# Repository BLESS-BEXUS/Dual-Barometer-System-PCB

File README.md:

<p align="center">
    <br>
    
</p>
<h1 align="center">Dual-Barometer System</h1>
<p align="center">
A compact PCB designed to provide wide-range pressure measurement, redundant sensing and onboard calibration for embedded systems where reliability, accuracy and easy integration are key.
</p>

<p align="center">

    <br>
    
</p>

---

### Overview

The main goal of this PCB is to improve the reliability and accuracy of pressure measurement in embedded sensing systems.

It is especially useful in applications where pressure conditions may vary significantly during operation and where a single commercial sensor may not provide enough range, resolution or calibration stability.

The board is designed to support:

- Wide-range pressure measurement.
- Redundant pressure sensing.
- Altitude estimation.
- Sensor cross-validation.
- Onboard calibration storage.
- Easy integration with a main controller.

### Main Features

- Dual-barometer architecture.
- TE MS5803-01BA high-resolution pressure sensor.
- Amphenol NPA-730B low-pressure backup sensor.
- Shared I2C communication bus.
- Onboard Microchip 24LC02B EEPROM.
- Storage of board-specific calibration coefficients.
- Plug-and-play calibration approach.
- Compact PCB for embedded sensing applications.
- Custom KiCad symbols, footprints and 3D models.

---

<h3 align="center">Contributing</h3>

<p align="center">
·
    <a href="./CODE_OF_CONDUCT.md">Code of Conduct</a>
    ·
    <a href="./CONTRIBUTING.md">Contributing Guide</a>
    ·
</p>

<p align="center">We welcome collaboration from the aerospace and software community. For major changes or data inquiries, please open an issue first.</p>

<h3 align="center">License</h3>

<pre align="center">Copyright © 2025-2026 The BLESS Project Team<br><br>This Source Code Form is subject to the terms of the Mozilla Public<br>License, v. 2.0. If a copy of the MPL was not distributed with this<br>file, You can obtain one at http://mozilla.org/MPL/2.0/.</pre>

<h3 align="center">Credits & Team</h3>

<p align="center">Supported by the REXUS/BEXUS Program and our generous sponsors.</p>
<p align="center">
    
</p>

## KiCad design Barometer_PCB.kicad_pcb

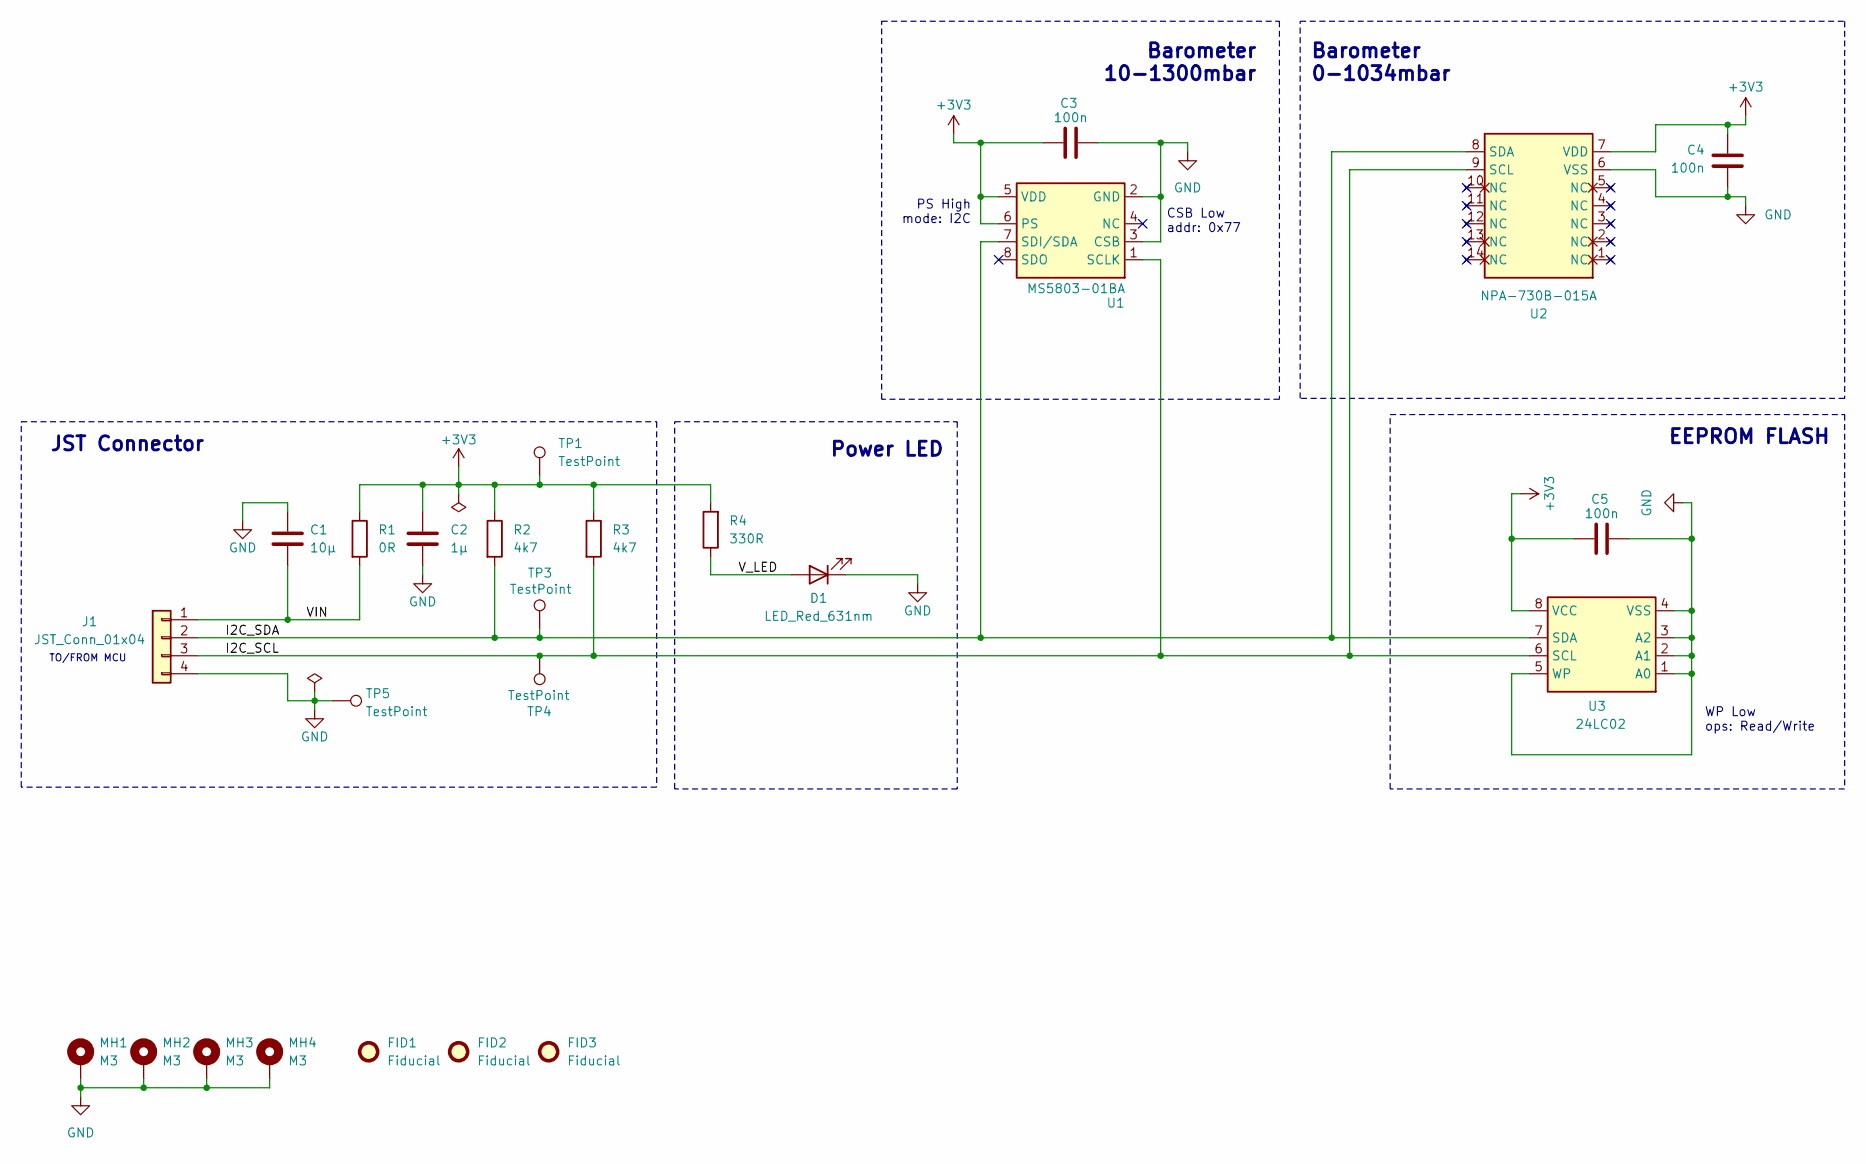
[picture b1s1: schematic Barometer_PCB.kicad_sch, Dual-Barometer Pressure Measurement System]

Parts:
C1: 10µ; C_1206_3216Metric; Manufacturer Part Number CGA5L1X7R1C106K160AC; LCSC C2168241
C2: 1µ; C_0805_2012Metric; Manufacturer Part Number KGM21AR71C105JU; LCSC C20219896
C3, C4, C5: 100n; C_0805_2012Metric; Manufacturer Part Number GCD21BR71H104KA01K; LCSC C21025875
D1: LED_Red_631nm; LED_0603_1608Metric; Manufacturer Part Number LTST-C190KRKT; LCSC C94869
FID1, FID2, FID3: Fiducial; Fiducial_1mm_Mask2mm
J1: JST_Conn_01x04; JST_SH_BM04B-SRSS-TB_1x04-1MP_P1.00mm_Vertical; Manufacturer Part Number BM04B-SRSS-TB(LF)(SN); LCSC C160390
MH1, MH2, MH3, MH4: M3; MountingHole_3.2mm_M3_Pad_Via
R1: 0R; R_0603_1608Metric; Manufacturer Part Number RC0603JR-070RL; LCSC C95177
R2, R3: 4k7; R_0805_2012Metric; Manufacturer Part Number AC0805JR-134K7L; LCSC C6457914
R4: 330R; R_0603_1608Metric; Manufacturer Part Number CR0603-FX-3300ELF; LCSC C2077087
TP1, TP3, TP4, TP5: TestPoint; TestPoint_Pad_D1.0mm
U1: MS5803-01BA; Manufacturer Part Number MS580301BA01-00; LCSC C5166409
U2: NPA-730B-015A; SOIC-14W_7.5x9mm_P1.27mm; Manufacturer Part Number NPA-730B-015A; LCSC C3253841
U3: 24LC02; SOIC-8_3.9x4.9mm_P1.27mm; Manufacturer Part Number 24LC02B-I/SN; LCSC C1348870

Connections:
+3V3: C2.1, C3.1, C4.1, C5.1, R1.1, R2.1, R3.1, R4.2, TP1.1, U1.5 (VDD), U1.6 (PS), U2.7 (VDD), U3.8 (VCC)
/I2C_SCL: J1.3, R3.2, TP4.1, U1.1 (SCLK), U2.9 (SCL), U3.6 (SCL)
/I2C_SDA: J1.2, R2.2, TP3.1, U1.7 (SDI/SDA), U2.8 (SDA), U3.7 (SDA)
/VIN: C1.1, J1.1, R1.2
/V_LED: D1.2 (A), R4.1
GND: C1.2, C2.2, C3.2, C4.2, C5.2, D1.1 (K), J1.4, MH1.1, MH2.1, MH3.1, MH4.1, TP5.1, U1.2 (GND), U1.3 (CSB), U2.6 (VSS), U3.1 (A0), U3.2 (A1), U3.3 (A2), U3.4 (VSS), U3.5 (WP); also elsewhere on the board

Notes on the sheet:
Barometer 10-1300mbar
Power LED
PS High mode: I2C
TO/FROM MCU
JST Connector
EEPROM FLASH
Barometer 0-1034mbar
WP Low ops: Read/Write
CSB Low addr: 0x77

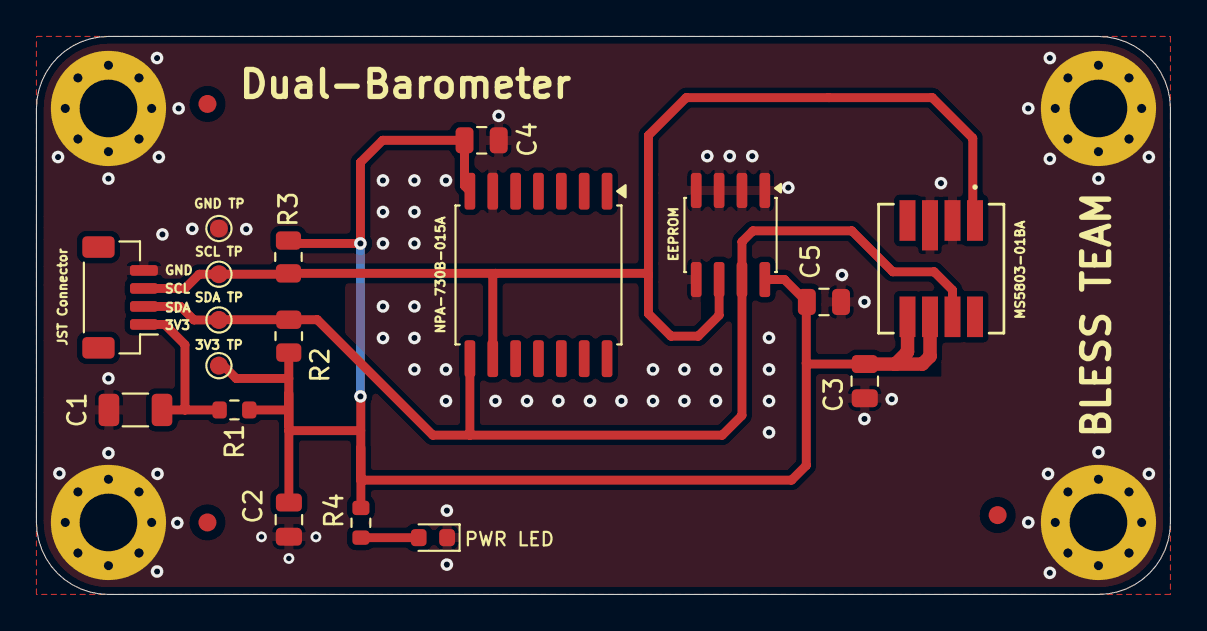
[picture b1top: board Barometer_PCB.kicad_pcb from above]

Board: 2 copper layers, 63.0 x 31.0 mm, 25 parts (0 on the bottom side), 6 nets.

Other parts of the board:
TP1#2: TestPoint; TestPoint_Pad_D1.0mm

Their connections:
GND: TP1#2.1; also elsewhere on the board

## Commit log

2026-06-12 Add .DS_Store to .gitignore for MacOS metadata files
2026-06-12 Add README.md and logo for Dual-Barometer System project
2026-06-12 Fix image URL in README.md for contributor badge
2026-06-12 Add initial barometer PCB KiCad project
2026-06-12 Add MS5803 footprint, symbol libraries and STEP model
2026-06-14 Fix DRC checks for GND
2026-06-14 JST pin and test point texts
